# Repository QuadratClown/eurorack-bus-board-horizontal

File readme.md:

# Eurorack Bus Board with horizontal headers

Minimalist eurorack bus-board with horizontal headers, made with focus on shallow skiffs, where each mm additional space matters.

## Features

8x 16-Pin headers in horizontal configuration. Allows pluging in cables from the side, which makes the footprint very thin (1.5cm) and the bus boards can be placed under the rails themselves.

Each rail (12V, -12V and 5V) is rated for 2A each, which should be easily enough for almost any usecase.

# To-do 

The via sizes are not optimal (hole too big, ring too small), hence the board would need revisiting.

It's still functional though :D

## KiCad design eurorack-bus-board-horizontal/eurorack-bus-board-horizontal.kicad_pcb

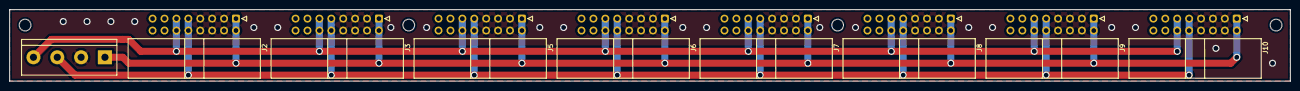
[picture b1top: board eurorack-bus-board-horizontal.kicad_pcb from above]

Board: 2 copper layers, 273.1 x 15.2 mm, 13 parts (0 on the bottom side), 4 nets.

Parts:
H1, H2, H3, H4: MountingHole; MountingHole_2.5mm
J1: Power In; TerminalBlock_bornier-4_P5.08mm
J2, J3, J5, J6, J7, J8, J9, J10: Euro 16-Pin; IDC-Header_2x08_P2.54mm_Horizontal_Quadrat

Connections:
+5V: J1.4, J2.11, J2.12, J3.11, J3.12, J5.11, J5.12, J6.11, J6.12, J7.11, J7.12, J8.11, J8.12, J9.11, J9.12, J10.11, J10.12
+12V: J1.3, J2.9, J2.10, J3.9, J3.10, J5.9, J5.10, J6.9, J6.10, J7.9, J7.10, J8.9, J8.10, J9.9, J9.10, J10.9, J10.10
-12V: J1.1, J2.1, J2.2, J3.1, J3.2, J5.1, J5.2, J6.1, J6.2, J7.1, J7.2, J8.1, J8.2, J9.1, J9.2, J10.1, J10.2
GND: J1.2, J2.3, J2.4, J2.5, J2.6, J2.7, J2.8, J3.3, J3.4, J3.5, J3.6, J3.7, J3.8, J5.3, J5.4, J5.5, J5.6, J5.7, J5.8, J6.3, J6.4, J6.5, J6.6, J6.7, J6.8, J7.3, J7.4, J7.5, J7.6, J7.7, J7.8, J8.3, J8.4, J8.5, J8.6, J8.7, J8.8, J9.3, J9.4, J9.5, J9.6, J9.7, J9.8, J10.3, J10.4, J10.5, J10.6, J10.7, J10.8

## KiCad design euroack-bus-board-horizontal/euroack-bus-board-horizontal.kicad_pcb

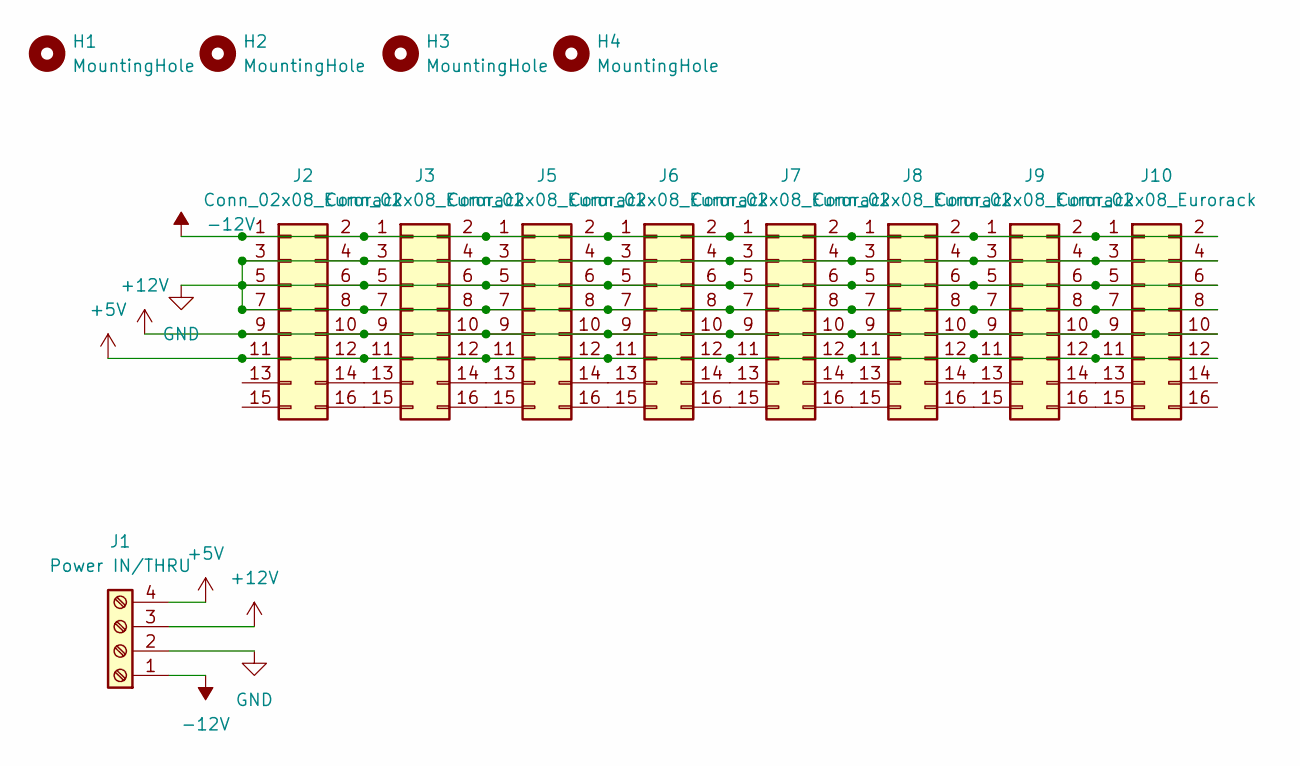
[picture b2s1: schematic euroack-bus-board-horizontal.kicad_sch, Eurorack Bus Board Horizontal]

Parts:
H1, H2, H3, H4: MountingHole; MountingHole_2.5mm
J1: Power IN/THRU; TerminalBlock_bornier-4_P5.08mm
J2, J3, J5, J6, J7, J8, J9, J10: Conn_02x08_Eurorack; IDC-Header_2x08_P2.54mm_Horizontal

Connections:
+5V: J1.4, J2.11, J2.12, J3.11, J3.12, J5.11, J5.12, J6.11, J6.12, J7.11, J7.12, J8.11, J8.12, J9.11, J9.12, J10.11, J10.12
+12V: J1.3, J2.9, J2.10, J3.9, J3.10, J5.9, J5.10, J6.9, J6.10, J7.9, J7.10, J8.9, J8.10, J9.9, J9.10, J10.9, J10.10
-12V: J1.1, J2.1, J2.2, J3.1, J3.2, J5.1, J5.2, J6.1, J6.2, J7.1, J7.2, J8.1, J8.2, J9.1, J9.2, J10.1, J10.2
GND: J1.2, J2.3, J2.4, J2.5, J2.6, J2.7, J2.8, J3.3, J3.4, J3.5, J3.6, J3.7, J3.8, J5.3, J5.4, J5.5, J5.6, J5.7, J5.8, J6.3, J6.4, J6.5, J6.6, J6.7, J6.8, J7.3, J7.4, J7.5, J7.6, J7.7, J7.8, J8.3, J8.4, J8.5, J8.6, J8.7, J8.8, J9.3, J9.4, J9.5, J9.6, J9.7, J9.8, J10.3, J10.4, J10.5, J10.6, J10.7, J10.8
unnamed: J2.14, J3.13
unnamed: J2.16, J3.15
unnamed: J3.14, J5.13
unnamed: J3.16, J5.15
unnamed: J5.14, J6.13
unnamed: J5.16, J6.15
unnamed: J6.14, J7.13
unnamed: J6.16, J7.15
unnamed: J7.14, J8.13
unnamed: J7.16, J8.15
unnamed: J8.14, J9.13
unnamed: J8.16, J9.15
unnamed: J9.14, J10.13
unnamed: J9.16, J10.15

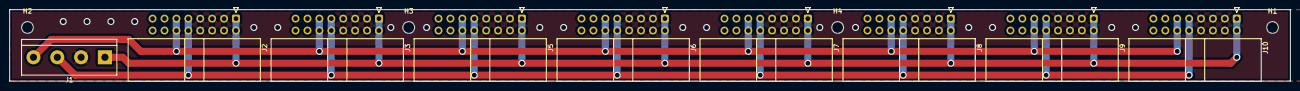
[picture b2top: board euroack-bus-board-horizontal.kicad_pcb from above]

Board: 2 copper layers, 273.1 x 15.2 mm, 13 parts (0 on the bottom side), 18 nets.

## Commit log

2022-11-07 fixed typo
2023-10-29 add additional files
2023-10-29 fix gitignore
2023-10-29 remove backups
